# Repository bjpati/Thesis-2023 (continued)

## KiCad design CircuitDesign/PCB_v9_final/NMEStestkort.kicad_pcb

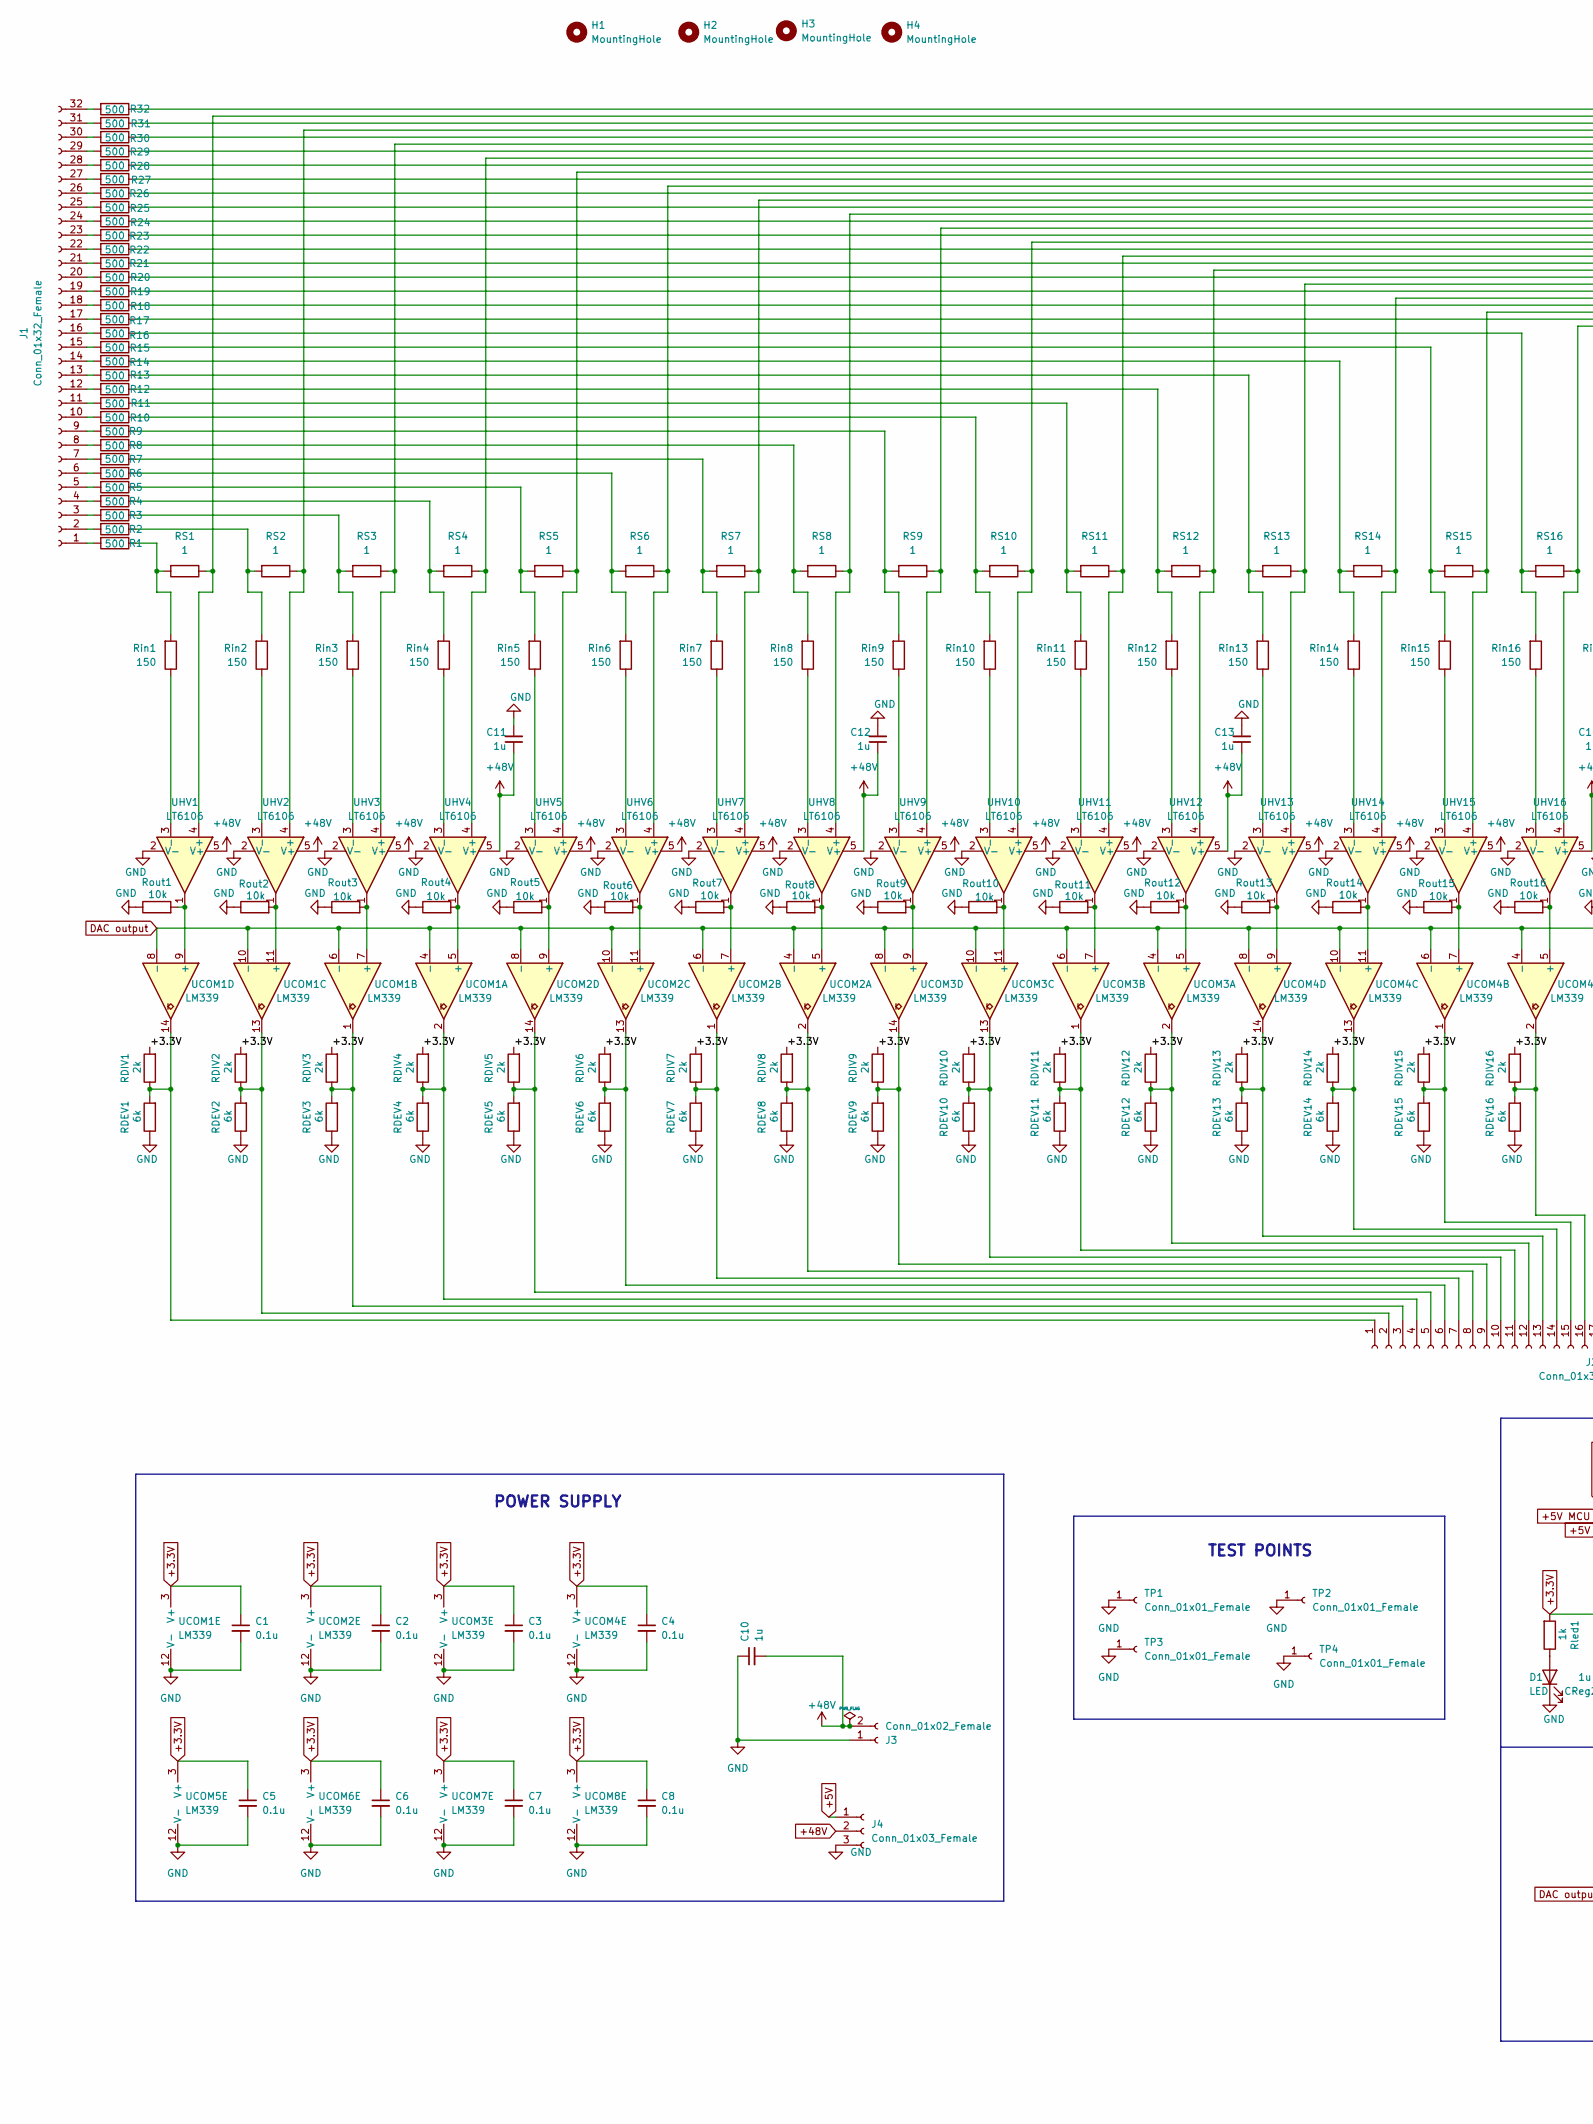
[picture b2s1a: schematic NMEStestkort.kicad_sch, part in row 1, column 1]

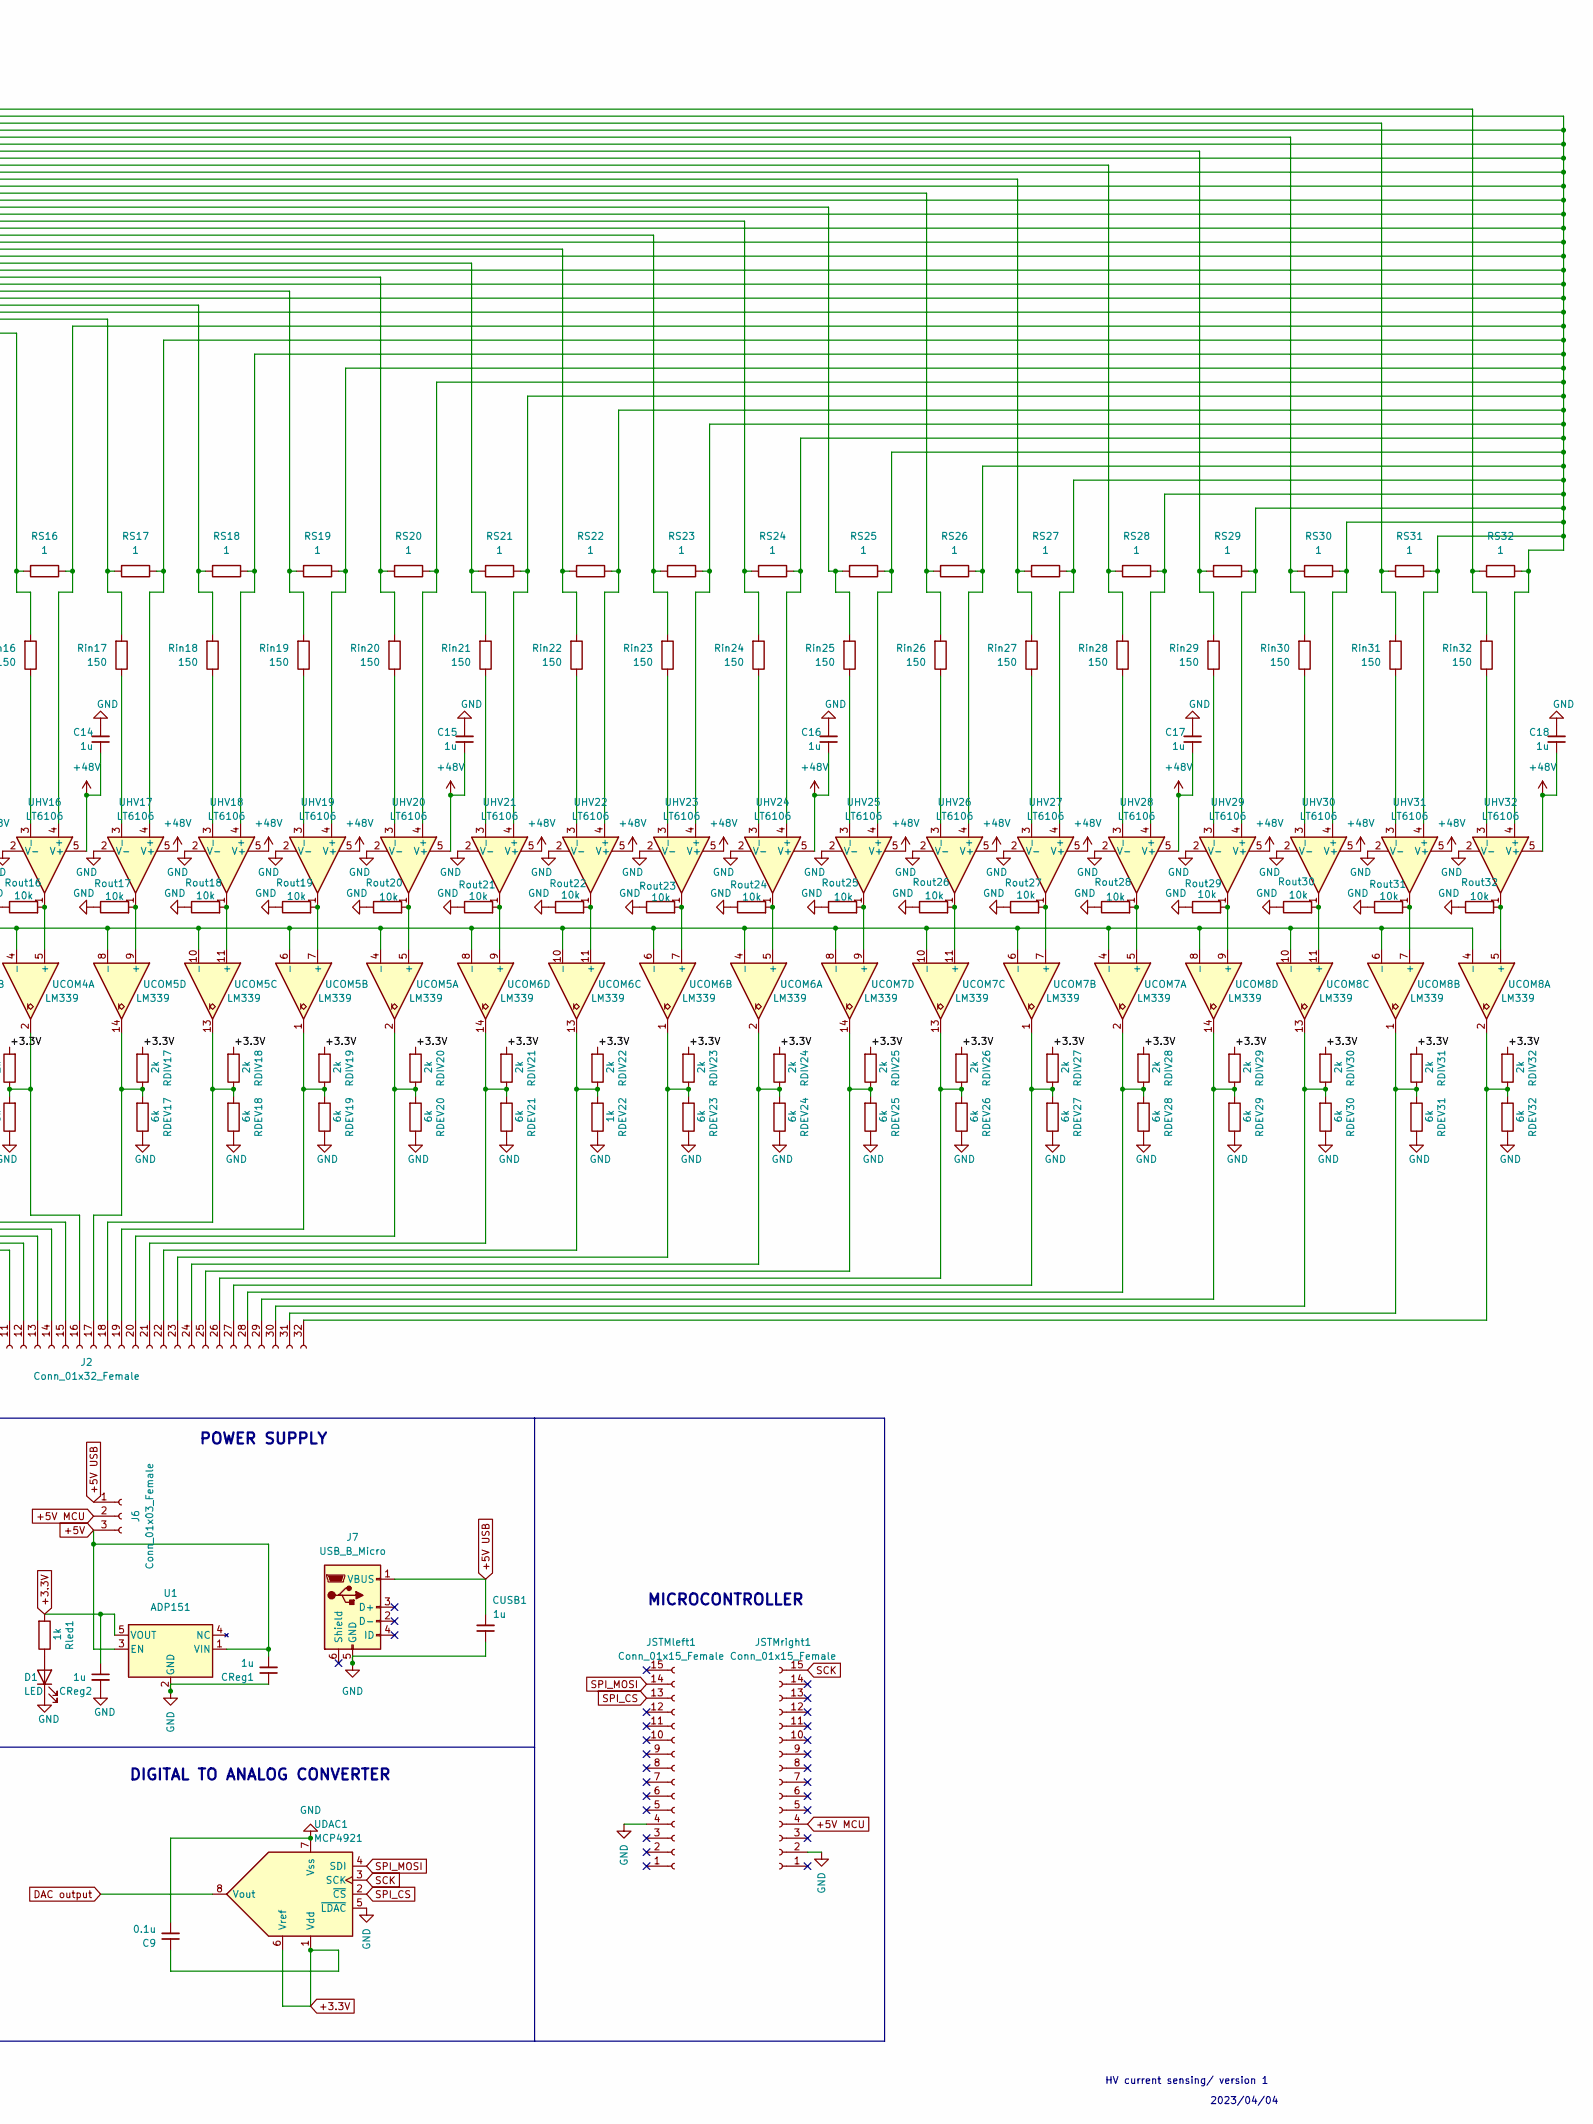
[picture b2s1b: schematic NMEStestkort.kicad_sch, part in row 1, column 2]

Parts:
C1, C2, C3, C4, C5, C6, C7, C8, C9: 0.1u; C_0805_2012Metric_Pad1.18x1.45mm_HandSolder
C10: 1u; C_0805_2012Metric_Pad1.18x1.45mm_HandSolder
C11, C12, C13, C14, C15, C16, C17, C18: 1u; CP_Elec_4x5.3
CReg1, CReg2: 1u; C_0805_2012Metric_Pad1.18x1.45mm_HandSolder
CUSB1: 1u; C_0805_2012Metric_Pad1.18x1.45mm_HandSolder
D1: LED; LED_1206_3216Metric_Pad1.42x1.75mm_HandSolder
H1, H2, H3, H4: MountingHole; MountingHole_3.5mm_Pad
J1, J2: Conn_01x32_Female; PinSocket_1x32_P2.54mm_Vertical
J3: Conn_01x02_Female; PinSocket_1x02_P2.54mm_Vertical
J4, J6: Conn_01x03_Female; PinSocket_1x03_P2.54mm_Vertical
J7: USB_B_Micro; USB_Micro-B_Molex_47346-0001
JSTMleft1: Conn_01x15_Female; PinSocket_1x15_P2.54mm_Vertical
JSTMright1: Conn_01x15_Female; PinSocket_1x15_P2.54mm_Vertical
R1, R2, R3, R4, R5, R6, R7, R8, R9, R10, R11, R12, R13, R14, R15, R16, R17, R18, R19, R20, R21, R22, R23, R24, R25, R26, R27, R28, R29, R30, R31, R32: 500; R_0603_1608Metric_Pad0.98x0.95mm_HandSolder
RDEV1, RDEV2, RDEV3, RDEV4, RDEV5, RDEV6, RDEV7, RDEV8, RDEV9, RDEV10, RDEV11, RDEV12, RDEV13, RDEV14, RDEV15, RDEV16, RDEV17, RDEV18, RDEV19, RDEV20, RDEV21, RDEV23, RDEV24, RDEV25, RDEV26, RDEV27, RDEV28, RDEV29, RDEV30, RDEV31, RDEV32: 6k; R_0603_1608Metric_Pad0.98x0.95mm_HandSolder
RDEV22: 1k; R_0603_1608Metric_Pad0.98x0.95mm_HandSolder
RDIV1, RDIV2, RDIV3, RDIV4, RDIV5, RDIV6, RDIV7, RDIV8, RDIV9, RDIV10, RDIV11, RDIV12, RDIV13, RDIV14, RDIV15, RDIV16, RDIV17, RDIV18, RDIV19, RDIV20, RDIV21, RDIV22, RDIV23, RDIV24, RDIV25, RDIV26, RDIV27, RDIV28, RDIV29, RDIV30, RDIV31, RDIV32: 2k; R_0603_1608Metric_Pad0.98x0.95mm_HandSolder
RS1, RS2, RS3, RS4, RS5, RS6, RS7, RS8, RS9, RS10, RS11, RS12, RS13, RS14, RS15, RS16, RS17, RS18, RS19, RS20, RS21, RS22, RS23, RS24, RS25, RS26, RS27, RS28, RS29, RS30, RS31, RS32: 1; R_0603_1608Metric_Pad0.98x0.95mm_HandSolder
Rin1, Rin2, Rin3, Rin4, Rin5, Rin6, Rin7, Rin8, Rin9, Rin10, Rin11, Rin12, Rin13, Rin14, Rin15, Rin16, Rin17, Rin18, Rin19, Rin20, Rin21, Rin22, Rin23, Rin24, Rin25, Rin26, Rin27, Rin28, Rin29, Rin30, Rin31, Rin32: 150; R_0603_1608Metric_Pad0.98x0.95mm_HandSolder
Rled1: 1k; R_0603_1608Metric_Pad0.98x0.95mm_HandSolder
Rout1, Rout2, Rout3, Rout4, Rout5, Rout6, Rout7, Rout8, Rout9, Rout10, Rout11, Rout12, Rout13, Rout14, Rout15, Rout16, Rout17, Rout18, Rout19, Rout20, Rout21, Rout22, Rout23, Rout24, Rout25, Rout26, Rout27, Rout28, Rout29, Rout30, Rout31, Rout32: 10k; R_0603_1608Metric_Pad0.98x0.95mm_HandSolder
TP1, TP2, TP3, TP4: Conn_01x01_Female; PinHeader_1x01_P2.54mm_Vertical
U1: ADP151; TSOT-23-5_HandSoldering
UCOM1, UCOM2, UCOM3, UCOM4, UCOM5, UCOM6, UCOM7, UCOM8: LM339; TSSOP-14_4.4x5mm_P0.65mm
UDAC1: MCP4921; MSOP-8_3x3mm_P0.65mm
UHV1, UHV2, UHV3, UHV4, UHV5, UHV6, UHV7, UHV8, UHV9, UHV10, UHV11, UHV12, UHV13, UHV14, UHV15, UHV16, UHV17, UHV18, UHV19, UHV20, UHV21, UHV22, UHV23, UHV24, UHV25, UHV26, UHV27, UHV28, UHV29, UHV30, UHV31, UHV32: LT6106; SOT-23-5_HandSoldering

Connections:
+3.3V: C1.1, C2.1, C3.1, C4.1, C5.1, C6.1, C7.1, C8.1, C9.1, CReg2.1, RDIV1.2, RDIV2.2, RDIV3.2, RDIV4.2, RDIV5.2, RDIV6.2, RDIV7.2, RDIV8.2, RDIV9.2, RDIV10.2, RDIV11.2, RDIV12.2, RDIV13.2, RDIV14.2, RDIV15.2, RDIV16.2, RDIV17.2, RDIV18.2, RDIV19.2, RDIV20.2, RDIV21.2, RDIV22.2, RDIV23.2, RDIV24.2, RDIV25.2, RDIV26.2, RDIV27.2, RDIV28.2, RDIV29.2, RDIV30.2, RDIV31.2, RDIV32.2, Rled1.2, U1.5 (VOUT), UCOM1.3 (V+), UCOM2.3 (V+), UCOM3.3 (V+), UCOM4.3 (V+), UCOM5.3 (V+), UCOM6.3 (V+), UCOM7.3 (V+), UCOM8.3 (V+), UDAC1.1 (Vdd), UDAC1.6 (Vref)
+5V: CReg1.2, J4.1, J6.3, U1.1 (VIN), U1.3 (EN)
+5V MCU: J6.2, JSTMright1.4
+5V USB: CUSB1.2, J6.1, J7.1 (VBUS)
+48V: C10.2, C11.1, C12.1, C13.1, C14.1, C15.1, C16.1, C17.1, C18.1, J3.2, J4.2, UHV1.5 (V+), UHV2.5 (V+), UHV3.5 (V+), UHV4.5 (V+), UHV5.5 (V+), UHV6.5 (V+), UHV7.5 (V+), UHV8.5 (V+), UHV9.5 (V+), UHV10.5 (V+), UHV11.5 (V+), UHV12.5 (V+), UHV13.5 (V+), UHV14.5 (V+), UHV15.5 (V+), UHV16.5 (V+), UHV17.5 (V+), UHV18.5 (V+), UHV19.5 (V+), UHV20.5 (V+), UHV21.5 (V+), UHV22.5 (V+), UHV23.5 (V+), UHV24.5 (V+), UHV25.5 (V+), UHV26.5 (V+), UHV27.5 (V+), UHV28.5 (V+), UHV29.5 (V+), UHV30.5 (V+), UHV31.5 (V+), UHV32.5 (V+)
DAC output: UCOM1.4 (-), UCOM1.6 (-), UCOM1.8 (-), UCOM1.10 (-), UCOM2.4 (-), UCOM2.6 (-), UCOM2.8 (-), UCOM2.10 (-), UCOM3.4 (-), UCOM3.6 (-), UCOM3.8 (-), UCOM3.10 (-), UCOM4.4 (-), UCOM4.6 (-), UCOM4.8 (-), UCOM4.10 (-), UCOM5.4 (-), UCOM5.6 (-), UCOM5.8 (-), UCOM5.10 (-), UCOM6.4 (-), UCOM6.6 (-), UCOM6.8 (-), UCOM6.10 (-), UCOM7.4 (-), UCOM7.6 (-), UCOM7.8 (-), UCOM7.10 (-), UCOM8.4 (-), UCOM8.6 (-), UCOM8.8 (-), UCOM8.10 (-), UDAC1.8 (Vout)
GND: C1.2, C2.2, C3.2, C4.2, C5.2, C6.2, C7.2, C8.2, C9.2, C10.1, C11.2, C12.2, C13.2, C14.2, C15.2, C16.2, C17.2, C18.2, CReg1.1, CReg2.2, CUSB1.1, D1.1 (K), J3.1, J4.3, J7.5 (GND), JSTMleft1.4, JSTMright1.2, RDEV1.1, RDEV2.1, RDEV3.1, RDEV4.1, RDEV5.1, RDEV6.1, RDEV7.1, RDEV8.1, RDEV9.1, RDEV10.1, RDEV11.1, RDEV12.1, RDEV13.1, RDEV14.1, RDEV15.1, RDEV16.1, RDEV17.1, RDEV18.1, RDEV19.1, RDEV20.1, RDEV21.1, RDEV22.1, RDEV23.1, RDEV24.1, RDEV25.1, RDEV26.1, RDEV27.1, RDEV28.1, RDEV29.1, RDEV30.1, RDEV31.1, RDEV32.1, Rout1.1, Rout2.1, Rout3.1, Rout4.1, Rout5.1, Rout6.1, Rout7.1, Rout8.1, Rout9.1, Rout10.1, Rout11.1, Rout12.1, Rout13.1, Rout14.1, Rout15.1, Rout16.1, Rout17.1, Rout18.1, Rout19.1, Rout20.1, Rout21.1, Rout22.1, Rout23.1, Rout24.1, Rout25.1, Rout26.1, Rout27.1, Rout28.1, Rout29.1, Rout30.1, Rout31.1, Rout32.1, TP1.1, TP2.1, TP3.1, TP4.1, U1.2 (GND), UCOM1.12 (V-), UCOM2.12 (V-), UCOM3.12 (V-), UCOM4.12 (V-), UCOM5.12 (V-), UCOM6.12 (V-), UCOM7.12 (V-), UCOM8.12 (V-), UDAC1.5 (~LDAC), UDAC1.7 (Vss), UHV1.2 (V-), UHV2.2 (V-), UHV3.2 (V-), UHV4.2 (V-), UHV5.2 (V-), UHV6.2 (V-), UHV7.2 (V-), UHV8.2 (V-), UHV9.2 (V-), UHV10.2 (V-), UHV11.2 (V-), UHV12.2 (V-), UHV13.2 (V-), UHV14.2 (V-), UHV15.2 (V-), UHV16.2 (V-), UHV17.2 (V-), UHV18.2 (V-), UHV19.2 (V-), UHV20.2 (V-), UHV21.2 (V-), UHV22.2 (V-), UHV23.2 (V-), UHV24.2 (V-), UHV25.2 (V-), UHV26.2 (V-), UHV27.2 (V-), UHV28.2 (V-), UHV29.2 (V-), UHV30.2 (V-), UHV31.2 (V-), UHV32.2 (V-)
unnamed: D1.2 (A), Rled1.1
unnamed: J1.1, R1.2
unnamed: J1.2, R2.2
unnamed: J1.3, R3.2
unnamed: J1.4, R4.2
unnamed: J1.5, R5.2
unnamed: J1.6, R6.2
unnamed: J1.7, R7.2
unnamed: J1.8, R8.2
unnamed: J1.9, R9.2
unnamed: J1.10, R10.2
unnamed: J1.11, R11.2
unnamed: J1.12, R12.2
unnamed: J1.13, R13.2
unnamed: J1.14, R14.2
unnamed: J1.15, R15.2
unnamed: J1.16, R16.2
unnamed: J1.17, R17.2
unnamed: J1.18, R18.2
unnamed: J1.19, R19.2
unnamed: J1.20, R20.2
unnamed: J1.21, R21.2
unnamed: J1.22, R22.2
unnamed: J1.23, R23.2
unnamed: J1.24, R24.2
unnamed: J1.25, R25.2
unnamed: J1.26, R26.2
unnamed: J1.27, R27.2
unnamed: J1.28, R28.2
unnamed: J1.29, R29.2
unnamed: J1.30, R30.2
unnamed: J1.31, R31.2
unnamed: J1.32, R32.2
unnamed: J2.1, RDEV1.2, RDIV1.1, UCOM1.14
unnamed: J2.2, RDEV2.2, RDIV2.1, UCOM1.13
unnamed: J2.3, RDEV3.2, RDIV3.1, UCOM1.1
unnamed: J2.4, RDEV4.2, RDIV4.1, UCOM1.2
unnamed: J2.5, RDEV5.2, RDIV5.1, UCOM2.14
unnamed: J2.6, RDEV6.2, RDIV6.1, UCOM2.13
unnamed: J2.7, RDEV7.2, RDIV7.1, UCOM2.1
unnamed: J2.8, RDEV8.2, RDIV8.1, UCOM2.2
unnamed: J2.9, RDEV9.2, RDIV9.1, UCOM3.14
unnamed: J2.10, RDEV10.2, RDIV10.1, UCOM3.13
unnamed: J2.11, RDEV11.2, RDIV11.1, UCOM3.1
unnamed: J2.12, RDEV12.2, RDIV12.1, UCOM3.2
unnamed: J2.13, RDEV13.2, RDIV13.1, UCOM4.14
unnamed: J2.14, RDEV14.2, RDIV14.1, UCOM4.13
unnamed: J2.15, RDEV15.2, RDIV15.1, UCOM4.1
unnamed: J2.16, RDEV16.2, RDIV16.1, UCOM4.2
unnamed: J2.17, RDEV17.2, RDIV17.1, UCOM5.14
unnamed: J2.18, RDEV18.2, RDIV18.1, UCOM5.13
unnamed: J2.19, RDEV19.2, RDIV19.1, UCOM5.1
unnamed: J2.20, RDEV20.2, RDIV20.1, UCOM5.2
unnamed: J2.21, RDEV21.2, RDIV21.1, UCOM6.14
unnamed: J2.22, RDEV22.2, RDIV22.1, UCOM6.13
unnamed: J2.23, RDEV23.2, RDIV23.1, UCOM6.1
unnamed: J2.24, RDEV24.2, RDIV24.1, UCOM6.2
unnamed: J2.25, RDEV25.2, RDIV25.1, UCOM7.14
unnamed: J2.26, RDEV26.2, RDIV26.1, UCOM7.13
unnamed: J2.27, RDEV27.2, RDIV27.1, UCOM7.1
unnamed: J2.28, RDEV28.2, RDIV28.1, UCOM7.2
unnamed: J2.29, RDEV29.2, RDIV29.1, UCOM8.14
unnamed: J2.30, RDEV30.2, RDIV30.1, UCOM8.13
unnamed: J2.31, RDEV31.2, RDIV31.1, UCOM8.1
unnamed: J2.32, RDEV32.2, RDIV32.1, UCOM8.2
unnamed: R1.1, RS1.2, Rin1.2
unnamed: R2.1, RS2.2, Rin2.2
unnamed: R3.1, RS3.2, Rin3.2
unnamed: R4.1, RS4.2, Rin4.2
unnamed: R5.1, RS5.2, Rin5.2
unnamed: R6.1, RS6.2, Rin6.2
unnamed: R7.1, RS7.2, Rin7.2
unnamed: R8.1, RS8.2, Rin8.2
unnamed: R9.1, RS9.2, Rin9.2
unnamed: R10.1, RS10.2, Rin10.2
unnamed: R11.1, RS11.2, Rin11.2
unnamed: R12.1, RS12.2, Rin12.2
unnamed: R13.1, RS13.2, Rin13.2
unnamed: R14.1, RS14.2, Rin14.2
unnamed: R15.1, RS15.2, Rin15.2
unnamed: R16.1, RS16.2, Rin16.2
unnamed: R17.1, RS17.2, Rin17.2
unnamed: R18.1, RS18.2, Rin18.2
unnamed: R19.1, RS19.2, Rin19.2
unnamed: R20.1, RS20.2, Rin20.2
unnamed: R21.1, RS21.2, Rin21.2
unnamed: R22.1, RS22.2, Rin22.2
unnamed: R23.1, RS23.2, Rin23.2
unnamed: R24.1, RS24.2, Rin24.2
unnamed: R25.1, RS25.2, Rin25.2
unnamed: R26.1, RS26.2, Rin26.2
unnamed: R27.1, RS27.2, Rin27.2
unnamed: R28.1, RS28.2, Rin28.2
unnamed: R29.1, RS29.2, Rin29.2
unnamed: R30.1, RS30.2, Rin30.2
unnamed: R31.1, RS31.2, Rin31.2
unnamed: R32.1, RS32.2, Rin32.2
unnamed: RS1.1, RS2.1, RS3.1, RS4.1, RS5.1, RS6.1, RS7.1, RS8.1, RS9.1, RS10.1, RS11.1, RS12.1, RS13.1, RS14.1, RS15.1, RS16.1, RS17.1, RS18.1, RS19.1, RS20.1, RS21.1, RS22.1, RS23.1, RS24.1, RS25.1, RS26.1, RS27.1, RS28.1, RS29.1, RS30.1, RS31.1, RS32.1, UHV1.4 (+), UHV2.4 (+), UHV3.4 (+), UHV4.4 (+), UHV5.4 (+), UHV6.4 (+), UHV7.4 (+), UHV8.4 (+), UHV9.4 (+), UHV10.4 (+), UHV11.4 (+), UHV12.4 (+), UHV13.4 (+), UHV14.4 (+), UHV15.4 (+), UHV16.4 (+), UHV17.4 (+), UHV18.4 (+), UHV19.4 (+), UHV20.4 (+), UHV21.4 (+), UHV22.4 (+), UHV23.4 (+), UHV24.4 (+), UHV25.4 (+), UHV26.4 (+), UHV27.4 (+), UHV28.4 (+), UHV29.4 (+), UHV30.4 (+), UHV31.4 (+), UHV32.4 (+)
unnamed: Rin1.1, UHV1.3 (-)
unnamed: Rin2.1, UHV2.3 (-)
unnamed: Rin3.1, UHV3.3 (-)
unnamed: Rin4.1, UHV4.3 (-)
unnamed: Rin5.1, UHV5.3 (-)
unnamed: Rin6.1, UHV6.3 (-)
unnamed: Rin7.1, UHV7.3 (-)
unnamed: Rin8.1, UHV8.3 (-)
unnamed: Rin9.1, UHV9.3 (-)
unnamed: Rin10.1, UHV10.3 (-)
unnamed: Rin11.1, UHV11.3 (-)
unnamed: Rin12.1, UHV12.3 (-)
unnamed: Rin13.1, UHV13.3 (-)
unnamed: Rin14.1, UHV14.3 (-)
unnamed: Rin15.1, UHV15.3 (-)
unnamed: Rin16.1, UHV16.3 (-)
unnamed: Rin17.1, UHV17.3 (-)
unnamed: Rin18.1, UHV18.3 (-)
unnamed: Rin19.1, UHV19.3 (-)
unnamed: Rin20.1, UHV20.3 (-)
unnamed: Rin21.1, UHV21.3 (-)
unnamed: Rin22.1, UHV22.3 (-)
unnamed: Rin23.1, UHV23.3 (-)
unnamed: Rin24.1, UHV24.3 (-)
unnamed: Rin25.1, UHV25.3 (-)
unnamed: Rin26.1, UHV26.3 (-)
unnamed: Rin27.1, UHV27.3 (-)
unnamed: Rin28.1, UHV28.3 (-)
unnamed: Rin29.1, UHV29.3 (-)
unnamed: Rin30.1, UHV30.3 (-)
unnamed: Rin31.1, UHV31.3 (-)
unnamed: Rin32.1, UHV32.3 (-)
unnamed: Rout1.2, UCOM1.9 (+), UHV1.1
unnamed: Rout2.2, UCOM1.11 (+), UHV2.1
unnamed: Rout3.2, UCOM1.7 (+), UHV3.1
unnamed: Rout4.2, UCOM1.5 (+), UHV4.1
unnamed: Rout5.2, UCOM2.9 (+), UHV5.1
unnamed: Rout6.2, UCOM2.11 (+), UHV6.1
unnamed: Rout7.2, UCOM2.7 (+), UHV7.1
unnamed: Rout8.2, UCOM2.5 (+), UHV8.1
unnamed: Rout9.2, UCOM3.9 (+), UHV9.1
unnamed: Rout10.2, UCOM3.11 (+), UHV10.1
unnamed: Rout11.2, UCOM3.7 (+), UHV11.1
unnamed: Rout12.2, UCOM3.5 (+), UHV12.1
unnamed: Rout13.2, UCOM4.9 (+), UHV13.1
unnamed: Rout14.2, UCOM4.11 (+), UHV14.1
unnamed: Rout15.2, UCOM4.7 (+), UHV15.1
unnamed: Rout16.2, UCOM4.5 (+), UHV16.1
unnamed: Rout17.2, UCOM5.9 (+), UHV17.1
unnamed: Rout18.2, UCOM5.11 (+), UHV18.1
unnamed: Rout19.2, UCOM5.7 (+), UHV19.1
unnamed: Rout20.2, UCOM5.5 (+), UHV20.1
unnamed: Rout21.2, UCOM6.9 (+), UHV21.1
unnamed: Rout22.2, UCOM6.11 (+), UHV22.1
unnamed: Rout23.2, UCOM6.7 (+), UHV23.1
unnamed: Rout24.2, UCOM6.5 (+), UHV24.1
unnamed: Rout25.2, UCOM7.9 (+), UHV25.1
unnamed: Rout26.2, UCOM7.11 (+), UHV26.1
unnamed: Rout27.2, UCOM7.7 (+), UHV27.1
unnamed: Rout28.2, UCOM7.5 (+), UHV28.1
unnamed: Rout29.2, UCOM8.9 (+), UHV29.1
unnamed: Rout30.2, UCOM8.11 (+), UHV30.1
unnamed: Rout31.2, UCOM8.7 (+), UHV31.1
unnamed: Rout32.2, UCOM8.5 (+), UHV32.1
SCK: JSTMright1.15, UDAC1.3 (SCK)
SPI_CS: JSTMleft1.13, UDAC1.2 (~CS)
SPI_MOSI: JSTMleft1.14, UDAC1.4 (SDI)

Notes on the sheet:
2023/04/04
HV current sensing/ version 1
POWER SUPPLY
DIGITAL TO ANALOG CONVERTER
TEST POINTS
MICROCONTROLLER

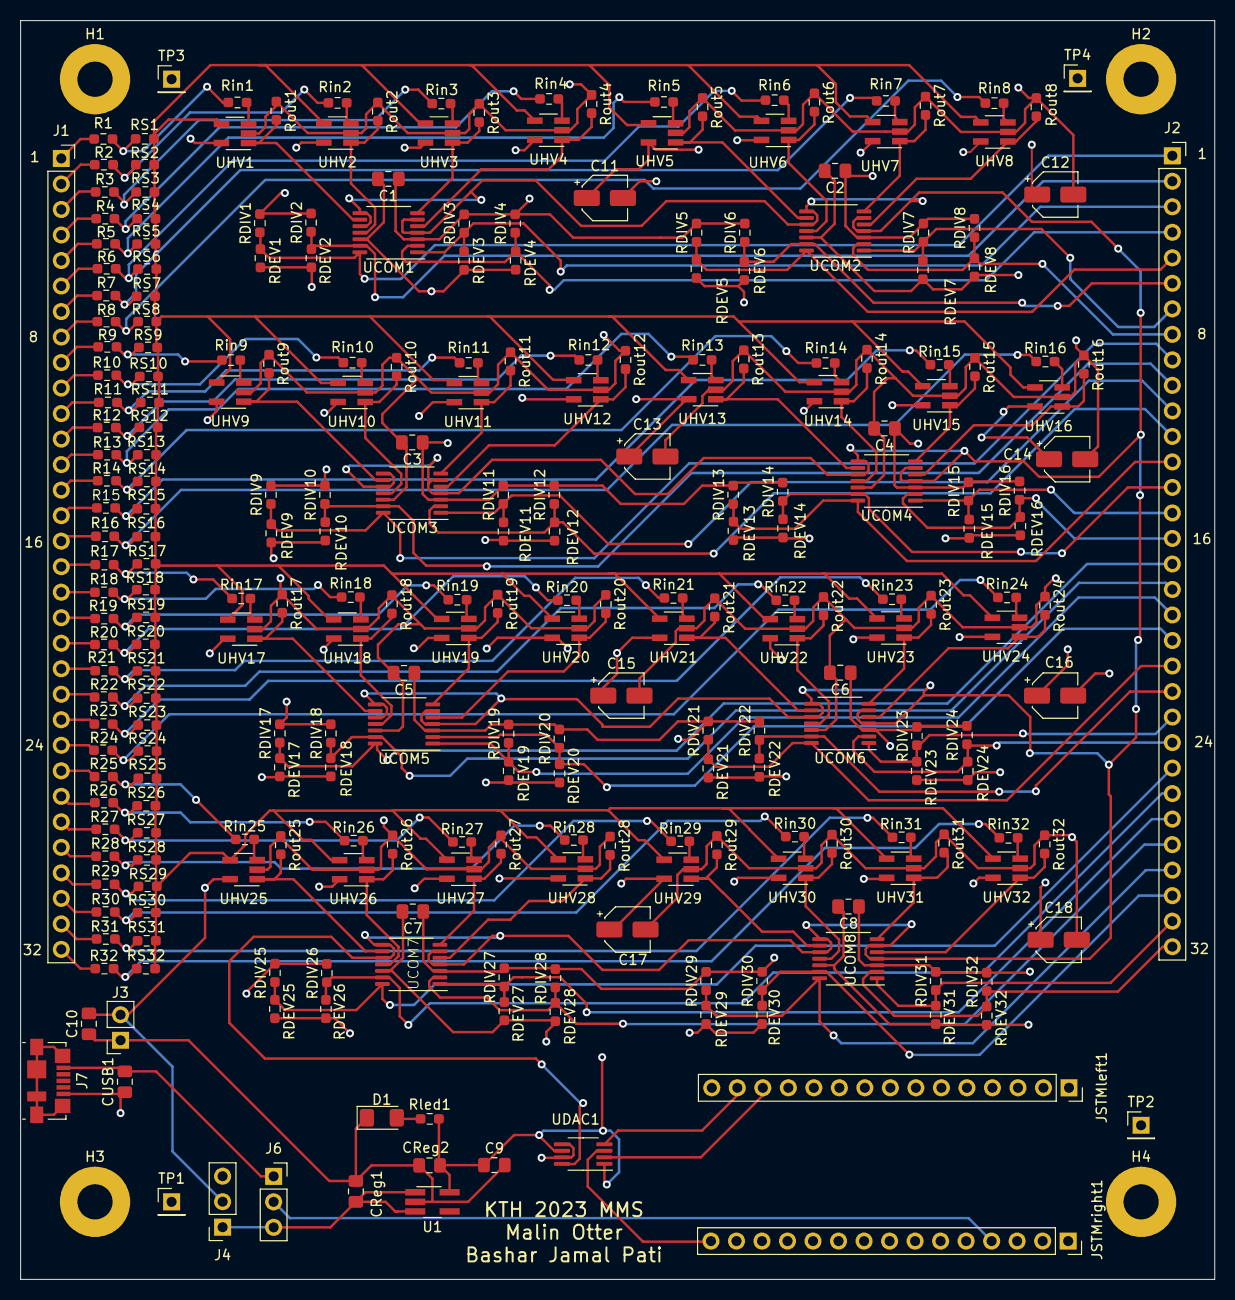
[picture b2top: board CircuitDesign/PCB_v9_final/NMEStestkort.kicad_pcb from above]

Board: 4 copper layers, 118.9 x 125.3 mm, 273 parts (0 on the bottom side), 172 nets.

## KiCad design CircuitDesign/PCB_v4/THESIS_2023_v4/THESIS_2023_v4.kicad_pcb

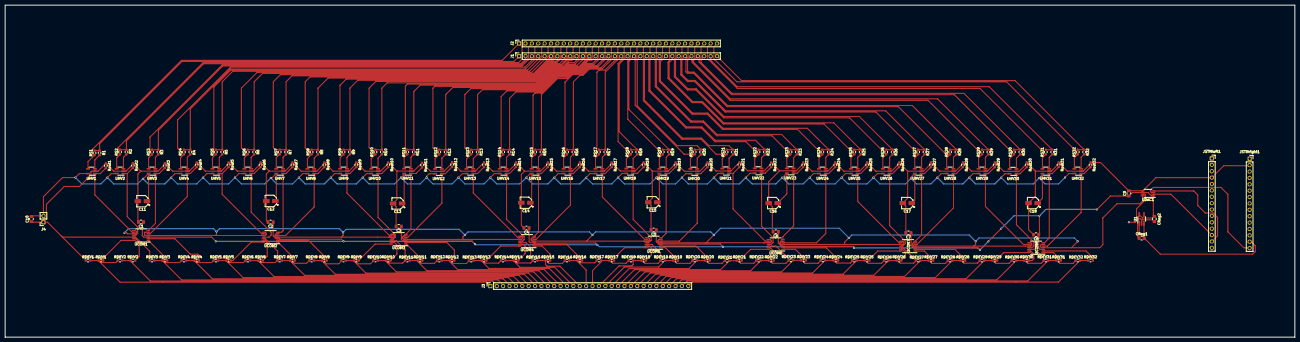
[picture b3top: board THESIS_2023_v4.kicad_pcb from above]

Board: 2 copper layers, 513.1 x 132.1 mm, 228 parts (0 on the bottom side), 200 nets.

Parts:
C1, C2, C3, C4, C5, C6, C7, C8, C10: 0.1u; C_0805_2012Metric_Pad1.18x1.45mm_HandSolder
C9: 1u; C_0805_2012Metric_Pad1.18x1.45mm_HandSolder
C11, C12, C13, C14, C15, C16, C17, C18: 1u; CP_Elec_4x5.3
CReg1, CReg2: 1u; C_0805_2012Metric_Pad1.18x1.45mm_HandSolder
J1, J2, J3: Conn_01x32_Female; PinSocket_1x32_P2.54mm_Vertical
J4: Conn_01x02_Female; PinSocket_1x02_P2.54mm_Vertical
JSTMleft1: Conn_01x15_Female; PinSocket_1x15_P2.54mm_Vertical
JSTMright1: Conn_01x15_Female; PinSocket_1x15_P2.54mm_Vertical
R1, R2, R3, R4, R5, R6, R7, R8, R9, R10, R11, R12, R13, R14, R15, R16, R17, R18, R19, R20, R21, R22, R23, R24, R25, R26, R27, R28, R29, R30, R31, R32: 150; R_0603_1608Metric_Pad0.98x0.95mm_HandSolder
RDEV1, RDEV2, RDEV3, RDEV4, RDEV5, RDEV6, RDEV7, RDEV8, RDEV9, RDEV10, RDEV11, RDEV12, RDEV13, RDEV14, RDEV15, RDEV16, RDEV17, RDEV18, RDEV19, RDEV20, RDEV21, RDEV22, RDEV23, RDEV24, RDEV25, RDEV26, RDEV27, RDEV28, RDEV29, RDEV30, RDEV31, RDEV32: 1k; R_0603_1608Metric_Pad0.98x0.95mm_HandSolder
RDIV1, RDIV2, RDIV3, RDIV4, RDIV5, RDIV6, RDIV7, RDIV8, RDIV9, RDIV10, RDIV11, RDIV12, RDIV13, RDIV14, RDIV15, RDIV16, RDIV17, RDIV18, RDIV19, RDIV20, RDIV21, RDIV22, RDIV23, RDIV24, RDIV25, RDIV26, RDIV27, RDIV28, RDIV29, RDIV30, RDIV31, RDIV32: 330; R_0603_1608Metric_Pad0.98x0.95mm_HandSolder
RS1, RS2, RS3, RS4, RS5, RS6, RS7, RS8, RS9, RS10, RS11, RS12, RS13, RS14, RS15, RS16, RS17, RS18, RS19, RS20, RS21, RS22, RS23, RS24, RS25, RS26, RS27, RS28, RS29, RS30, RS31, RS32: 1; R_0603_1608Metric_Pad0.98x0.95mm_HandSolder
Rout1, Rout2, Rout3, Rout4, Rout5, Rout6, Rout7, Rout8, Rout9, Rout10, Rout11, Rout12, Rout13, Rout14, Rout15, Rout16, Rout17, Rout18, Rout19, Rout20, Rout21, Rout22, Rout23, Rout24, Rout25, Rout26, Rout27, Rout28, Rout29, Rout30, Rout31, Rout32: 10k; R_0603_1608Metric_Pad0.98x0.95mm_HandSolder
U1: LK112M15TR; TSOT-23-5_HandSoldering
UCOM1, UCOM2, UCOM3, UCOM4, UCOM5, UCOM6, UCOM7, UCOM8: LM339; TSSOP-14_4.4x5mm_P0.65mm
UDAC1: MCP4921; MSOP-8_3x3mm_P0.65mm
UHV1, UHV2, UHV3, UHV4, UHV5, UHV6, UHV7, UHV8, UHV9, UHV10, UHV11, UHV12, UHV13, UHV14, UHV15, UHV16, UHV17, UHV18, UHV19, UHV20, UHV21, UHV22, UHV23, UHV24, UHV25, UHV26, UHV27, UHV28, UHV29, UHV30, UHV31, UHV32: LT6106; SOT-23-5_HandSoldering

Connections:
+3V3: CReg1.2, JSTMright1.14, U1.1 (SHDN), U1.3 (Bypass)
+48V: C10.2, C11.1, C12.1, C13.1, C14.1, C15.1, C16.1, C17.1, C18.1, J4.2, UHV1.5 (V+), UHV2.5 (V+), UHV3.5 (V+), UHV4.5 (V+), UHV5.5 (V+), UHV6.5 (V+), UHV7.5 (V+), UHV8.5 (V+), UHV9.5 (V+), UHV10.5 (V+), UHV11.5 (V+), UHV12.5 (V+), UHV13.5 (V+), UHV14.5 (V+), UHV15.5 (V+), UHV16.5 (V+), UHV17.5 (V+), UHV18.5 (V+), UHV19.5 (V+), UHV20.5 (V+), UHV21.5 (V+), UHV22.5 (V+), UHV23.5 (V+), UHV24.5 (V+), UHV25.5 (V+), UHV26.5 (V+), UHV27.5 (V+), UHV28.5 (V+), UHV29.5 (V+), UHV30.5 (V+), UHV31.5 (V+), UHV32.5 (V+)
/+3.3V: C1.1, C2.1, C3.1, C4.1, C5.1, C6.1, C7.1, C8.1, C9.1, CReg2.1, U1.5 (IN), UCOM1.3 (V+), UCOM2.3 (V+), UCOM3.3 (V+), UCOM4.3 (V+), UCOM5.3 (V+), UCOM6.3 (V+), UCOM7.3 (V+), UCOM8.3 (V+), UDAC1.1 (Vdd), UDAC1.6 (Vref)
GND: C1.2, C2.2, C3.2, C4.2, C5.2, C6.2, C7.2, C8.2, C9.2, C10.1, C11.2, C12.2, C13.2, C14.2, C15.2, C16.2, C17.2, C18.2, CReg1.1, CReg2.2, J4.1, JSTMleft1.4, JSTMright1.2, RDEV1.1, RDEV2.1, RDEV3.1, RDEV4.1, RDEV5.1, RDEV6.1, RDEV7.1, RDEV8.1, RDEV9.1, RDEV10.1, RDEV11.1, RDEV12.1, RDEV13.1, RDEV14.1, RDEV15.1, RDEV16.1, RDEV17.1, RDEV18.1, RDEV19.1, RDEV20.1, RDEV21.1, RDEV22.1, RDEV23.1, RDEV24.1, RDEV25.1, RDEV26.1, RDEV27.1, RDEV28.1, RDEV29.1, RDEV30.1, RDEV31.1, RDEV32.1, Rout1.1, Rout2.1, Rout3.1, Rout4.1, Rout5.1, Rout6.1, Rout7.1, Rout8.1, Rout9.1, Rout10.1, Rout11.1, Rout12.1, Rout13.1, Rout14.1, Rout15.1, Rout16.1, Rout17.1, Rout18.1, Rout19.1, Rout20.1, Rout21.1, Rout22.1, Rout23.1, Rout24.1, Rout25.1, Rout26.1, Rout27.1, Rout28.1, Rout29.1, Rout30.1, Rout31.1, Rout32.1, U1.2 (GND), UCOM1.12 (V-), UCOM2.12 (V-), UCOM3.12 (V-), UCOM4.12 (V-), UCOM5.12 (V-), UCOM6.12 (V-), UCOM7.12 (V-), UCOM8.12 (V-), UDAC1.5 (~LDAC), UDAC1.7 (Vss), UHV1.2 (V-), UHV2.2 (V-), UHV3.2 (V-), UHV4.2 (V-), UHV5.2 (V-), UHV6.2 (V-), UHV7.2 (V-), UHV8.2 (V-), UHV9.2 (V-), UHV10.2 (V-), UHV11.2 (V-), UHV12.2 (V-), UHV13.2 (V-), UHV14.2 (V-), UHV15.2 (V-), UHV16.2 (V-), UHV17.2 (V-), UHV18.2 (V-), UHV19.2 (V-), UHV20.2 (V-), UHV21.2 (V-), UHV22.2 (V-), UHV23.2 (V-), UHV24.2 (V-), UHV25.2 (V-), UHV26.2 (V-), UHV27.2 (V-), UHV28.2 (V-), UHV29.2 (V-), UHV30.2 (V-), UHV31.2 (V-), UHV32.2 (V-)
unnamed: J1.1, R1.2, RS1.2
unnamed: J1.2, R2.2, RS2.2
unnamed: J1.3, R3.2, RS3.2
unnamed: J1.4, R4.2, RS4.2
unnamed: J1.5, R5.2, RS5.2
unnamed: J1.6, R6.2, RS6.2
unnamed: J1.7, R7.2, RS7.2
unnamed: J1.8, R8.2, RS8.2
unnamed: J1.9, R9.2, RS9.2
unnamed: J1.10, R10.2, RS10.2
unnamed: J1.11, R11.2, RS11.2
unnamed: J1.12, R12.2, RS12.2
unnamed: J1.13, R13.2, RS13.2
unnamed: J1.14, R14.2, RS14.2
unnamed: J1.15, R15.2, RS15.2
unnamed: J1.16, R16.2, RS16.2
unnamed: J1.17, R17.2, RS17.2
unnamed: J1.18, R18.2, RS18.2
unnamed: J1.19, R19.2, RS19.2
unnamed: J1.20, R20.2, RS20.2
unnamed: J1.21, R21.2, RS21.2
unnamed: J1.22, R22.2, RS22.2
unnamed: J1.23, R23.2, RS23.2
unnamed: J1.24, R24.2, RS24.2
unnamed: J1.25, R25.2, RS25.2
unnamed: J1.26, R26.2, RS26.2
unnamed: J1.27, R27.2, RS27.2
unnamed: J1.28, R28.2, RS28.2
unnamed: J1.29, R29.2, RS29.2
unnamed: J1.30, R30.2, RS30.2
unnamed: J1.31, R31.2, RS31.2
unnamed: J1.32, R32.2, RS32.2
unnamed: J2.1, RS1.1, UHV1.4 (+)
unnamed: J2.2, RS2.1, UHV2.4 (+)
unnamed: J2.3, RS3.1, UHV3.4 (+)
unnamed: J2.4, RS4.1, UHV4.4 (+)
unnamed: J2.5, RS5.1, UHV5.4 (+)
unnamed: J2.6, RS6.1, UHV6.4 (+)
unnamed: J2.7, RS7.1, UHV7.4 (+)
unnamed: J2.8, RS8.1, UHV8.4 (+)
unnamed: J2.9, RS9.1, UHV9.4 (+)
unnamed: J2.10, RS10.1, UHV10.4 (+)
unnamed: J2.11, RS11.1, UHV11.4 (+)
unnamed: J2.12, RS12.1, UHV12.4 (+)
unnamed: J2.13, RS13.1, UHV13.4 (+)
unnamed: J2.14, RS14.1, UHV14.4 (+)
unnamed: J2.15, RS15.1, UHV15.4 (+)
unnamed: J2.16, RS16.1, UHV16.4 (+)
unnamed: J2.17, RS17.1, UHV17.4 (+)
unnamed: J2.18, RS18.1, UHV18.4 (+)
unnamed: J2.19, RS19.1, UHV19.4 (+)
unnamed: J2.20, RS20.1, UHV20.4 (+)
unnamed: J2.21, RS21.1, UHV21.4 (+)
unnamed: J2.22, RS22.1, UHV22.4 (+)
unnamed: J2.23, RS23.1, UHV23.4 (+)
unnamed: J2.24, RS24.1, UHV24.4 (+)
unnamed: J2.25, RS25.1, UHV25.4 (+)
unnamed: J2.26, RS26.1, UHV26.4 (+)
unnamed: J2.27, RS27.1, UHV27.4 (+)
unnamed: J2.28, RS28.1, UHV28.4 (+)
unnamed: J2.29, RS29.1, UHV29.4 (+)
unnamed: J2.30, RS30.1, UHV30.4 (+)
unnamed: J2.31, RS31.1, UHV31.4 (+)
unnamed: J2.32, RS32.1, UHV32.4 (+)
unnamed: J3.1, RDEV1.2, RDIV1.1
unnamed: J3.2, RDEV2.2, RDIV2.1
unnamed: J3.3, RDEV3.2, RDIV3.1
unnamed: J3.4, RDEV4.2, RDIV4.1
unnamed: J3.5, RDEV5.2, RDIV5.1
unnamed: J3.6, RDEV6.2, RDIV6.1
unnamed: J3.7, RDEV7.2, RDIV7.1
unnamed: J3.8, RDEV8.2, RDIV8.1
unnamed: J3.9, RDEV9.2, RDIV9.1
unnamed: J3.10, RDEV10.2, RDIV10.1
unnamed: J3.11, RDEV11.2, RDIV11.1
unnamed: J3.12, RDEV12.2, RDIV12.1
unnamed: J3.13, RDEV13.2, RDIV13.1
unnamed: J3.14, RDEV14.2, RDIV14.1
unnamed: J3.15, RDEV15.2, RDIV15.1
unnamed: J3.16, RDEV16.2, RDIV16.1
unnamed: J3.17, RDEV17.2, RDIV17.1
unnamed: J3.18, RDEV18.2, RDIV18.1
unnamed: J3.19, RDEV19.2, RDIV19.1
unnamed: J3.20, RDEV20.2, RDIV20.1
unnamed: J3.21, RDEV21.2, RDIV21.1
unnamed: J3.22, RDEV22.2, RDIV22.1
unnamed: J3.23, RDEV23.2, RDIV23.1
unnamed: J3.24, RDEV24.2, RDIV24.1
unnamed: J3.25, RDEV25.2, RDIV25.1
unnamed: J3.26, RDEV26.2, RDIV26.1
unnamed: J3.27, RDEV27.2, RDIV27.1
unnamed: J3.28, RDEV28.2, RDIV28.1
unnamed: J3.29, RDEV29.2, RDIV29.1
unnamed: J3.30, RDEV30.2, RDIV30.1
unnamed: J3.31, RDEV31.2, RDIV31.1
unnamed: J3.32, RDEV32.2, RDIV32.1
unnamed: JSTMleft1.13, UDAC1.2 (~CS)
unnamed: JSTMleft1.14, UDAC1.4 (SDI)
unnamed: JSTMright1.15, UDAC1.3 (SCK)
unnamed: R1.1, UHV1.3 (-)
unnamed: R2.1, UHV2.3 (-)
unnamed: R3.1, UHV3.3 (-)
unnamed: R4.1, UHV4.3 (-)
unnamed: R5.1, UHV5.3 (-)
unnamed: R6.1, UHV6.3 (-)
unnamed: R7.1, UHV7.3 (-)
unnamed: R8.1, UHV8.3 (-)
unnamed: R9.1, UHV9.3 (-)
unnamed: R10.1, UHV10.3 (-)
unnamed: R11.1, UHV11.3 (-)
unnamed: R12.1, UHV12.3 (-)
unnamed: R13.1, UHV13.3 (-)
unnamed: R14.1, UHV14.3 (-)
unnamed: R15.1, UHV15.3 (-)
unnamed: R16.1, UHV16.3 (-)
unnamed: R17.1, UHV17.3 (-)
unnamed: R18.1, UHV18.3 (-)
unnamed: R19.1, UHV19.3 (-)
unnamed: R20.1, UHV20.3 (-)
unnamed: R21.1, UHV21.3 (-)
unnamed: R22.1, UHV22.3 (-)
unnamed: R23.1, UHV23.3 (-)
unnamed: R24.1, UHV24.3 (-)
unnamed: R25.1, UHV25.3 (-)
unnamed: R26.1, UHV26.3 (-)
unnamed: R27.1, UHV27.3 (-)
unnamed: R28.1, UHV28.3 (-)
unnamed: R29.1, UHV29.3 (-)
unnamed: R30.1, UHV30.3 (-)
unnamed: R31.1, UHV31.3 (-)
unnamed: R32.1, UHV32.3 (-)
unnamed: RDIV1.2, UCOM1.14
unnamed: RDIV2.2, UCOM1.13
unnamed: RDIV3.2, UCOM1.1
unnamed: RDIV4.2, UCOM1.2
unnamed: RDIV5.2, UCOM2.14
unnamed: RDIV6.2, UCOM2.13
unnamed: RDIV7.2, UCOM2.1
unnamed: RDIV8.2, UCOM2.2
unnamed: RDIV9.2, UCOM3.14
unnamed: RDIV10.2, UCOM3.13
unnamed: RDIV11.2, UCOM3.1
unnamed: RDIV12.2, UCOM3.2
unnamed: RDIV13.2, UCOM4.14
unnamed: RDIV14.2, UCOM4.13
unnamed: RDIV15.2, UCOM4.1
unnamed: RDIV16.2, UCOM4.2
unnamed: RDIV17.2, UCOM5.14
unnamed: RDIV18.2, UCOM5.13
unnamed: RDIV19.2, UCOM5.1
unnamed: RDIV20.2, UCOM5.2
unnamed: RDIV21.2, UCOM6.14
unnamed: RDIV22.2, UCOM6.13
unnamed: RDIV23.2, UCOM6.1
unnamed: RDIV24.2, UCOM6.2
unnamed: RDIV25.2, UCOM7.14
unnamed: RDIV26.2, UCOM7.13
unnamed: RDIV27.2, UCOM7.1
unnamed: RDIV28.2, UCOM7.2
unnamed: RDIV29.2, UCOM8.14
unnamed: RDIV30.2, UCOM8.13
unnamed: RDIV31.2, UCOM8.1
unnamed: RDIV32.2, UCOM8.2
unnamed: Rout1.2, UCOM1.9 (+), UHV1.1
unnamed: Rout2.2, UCOM1.11 (+), UHV2.1
unnamed: Rout3.2, UCOM1.7 (+), UHV3.1
unnamed: Rout4.2, UCOM1.5 (+), UHV4.1
unnamed: Rout5.2, UCOM2.9 (+), UHV5.1
unnamed: Rout6.2, UCOM2.11 (+), UHV6.1
unnamed: Rout7.2, UCOM2.7 (+), UHV7.1
unnamed: Rout8.2, UCOM2.5 (+), UHV8.1
unnamed: Rout9.2, UCOM3.9 (+), UHV9.1
unnamed: Rout10.2, UCOM3.11 (+), UHV10.1
unnamed: Rout11.2, UCOM3.7 (+), UHV11.1
unnamed: Rout12.2, UCOM3.5 (+), UHV12.1
unnamed: Rout13.2, UCOM4.9 (+), UHV13.1
unnamed: Rout14.2, UCOM4.11 (+), UHV14.1
unnamed: Rout15.2, UCOM4.7 (+), UHV15.1
unnamed: Rout16.2, UCOM4.5 (+), UHV16.1
unnamed: Rout17.2, UCOM5.9 (+), UHV17.1
unnamed: Rout18.2, UCOM5.11 (+), UHV18.1
unnamed: Rout19.2, UCOM5.7 (+), UHV19.1
unnamed: Rout20.2, UCOM5.5 (+), UHV20.1
unnamed: Rout21.2, UCOM6.9 (+), UHV21.1
unnamed: Rout22.2, UCOM6.11 (+), UHV22.1
unnamed: Rout23.2, UCOM6.7 (+), UHV23.1
unnamed: Rout24.2, UCOM6.5 (+), UHV24.1
unnamed: Rout25.2, UCOM7.9 (+), UHV25.1
unnamed: Rout26.2, UCOM7.11 (+), UHV26.1
unnamed: Rout27.2, UCOM7.7 (+), UHV27.1
unnamed: Rout28.2, UCOM7.5 (+), UHV28.1
unnamed: Rout29.2, UCOM8.9 (+), UHV29.1
unnamed: Rout30.2, UCOM8.11 (+), UHV30.1
unnamed: Rout31.2, UCOM8.7 (+), UHV31.1
unnamed: Rout32.2, UCOM8.5 (+), UHV32.1
unnamed: UCOM1.4 (-), UCOM1.6 (-), UCOM1.8 (-), UCOM1.10 (-), UCOM2.4 (-), UCOM2.6 (-), UCOM2.8 (-), UCOM2.10 (-), UCOM3.4 (-), UCOM3.6 (-), UCOM3.8 (-), UCOM3.10 (-), UCOM4.4 (-), UCOM4.6 (-), UCOM4.8 (-), UCOM4.10 (-), UCOM5.4 (-), UCOM5.6 (-), UCOM5.8 (-), UCOM5.10 (-), UCOM6.4 (-), UCOM6.6 (-), UCOM6.8 (-), UCOM6.10 (-), UCOM7.4 (-), UCOM7.6 (-), UCOM7.8 (-), UCOM7.10 (-), UCOM8.4 (-), UCOM8.6 (-), UCOM8.8 (-), UCOM8.10 (-), UDAC1.8 (Vout)

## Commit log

2023-04-11 text
2023-04-11 Changed
2023-04-11 put all PCB in same folder
2023-04-12 Update 04/12
2023-04-24 PCB update
2023-05-03 Update with final PCB version
2023-05-19 Update with new version (IA)
2023-05-22 update with the final version
2023-06-22 Update the code
2023-06-22 Update name
